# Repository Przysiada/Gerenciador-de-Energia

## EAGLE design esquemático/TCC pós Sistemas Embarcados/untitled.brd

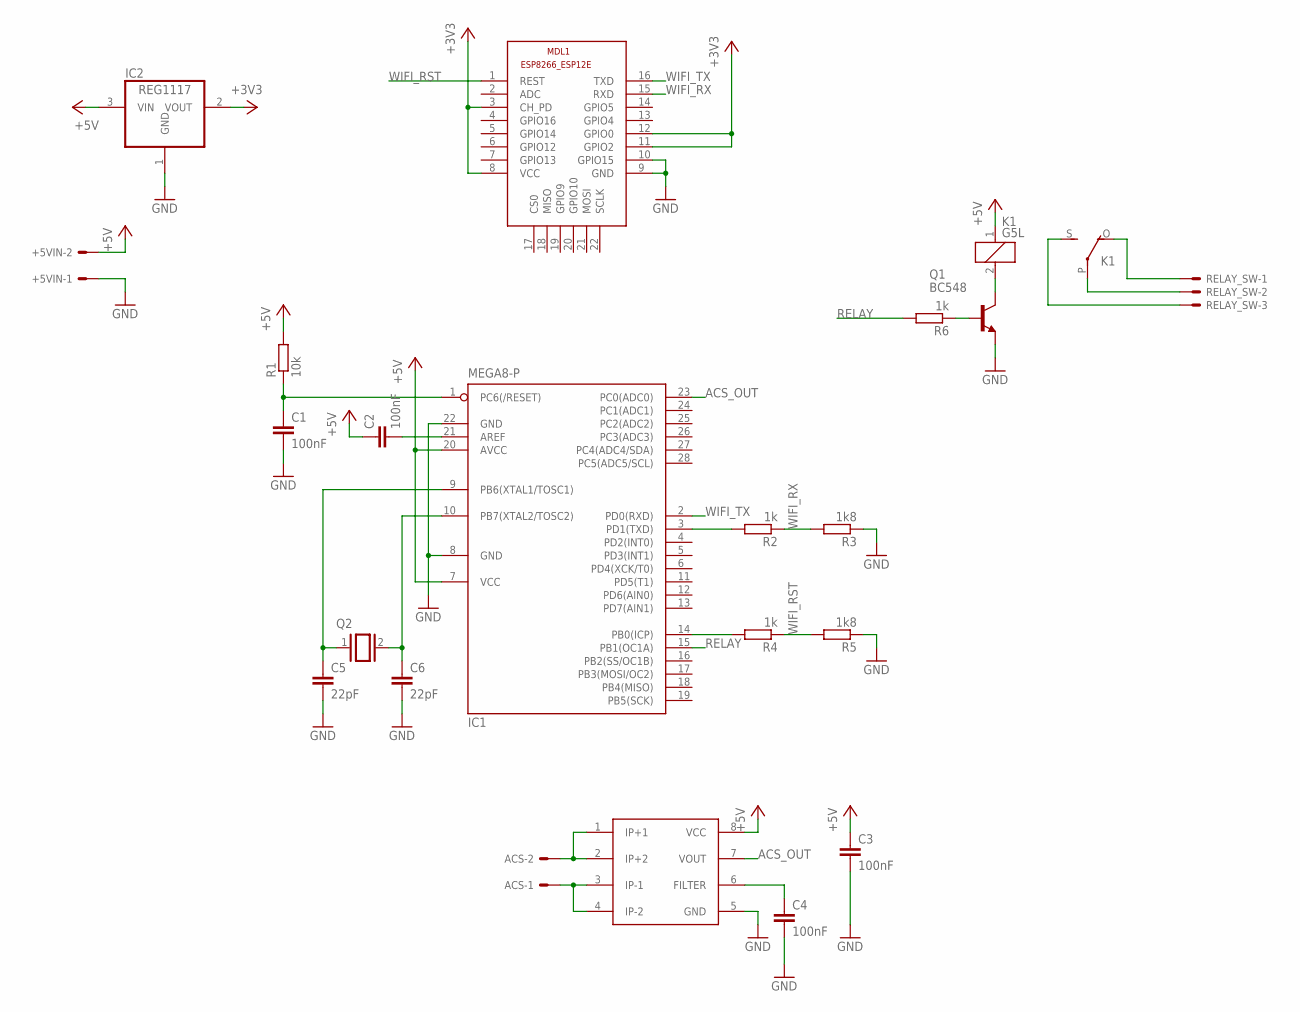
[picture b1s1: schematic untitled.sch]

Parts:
+5VIN: KK-156-2
ACS: KK-156-2
C1, C2, C3, C4: 100nF; C050-030X075
C5, C6: 22pF; C050-030X075
IC1: MEGA8-P; DIL28-3
IC2: REG1117; SOT223
K1: G5L; G5LE
MDL1: ESP8266-12EESP8266-ESP12E; ESP8266-ESP12E
Q1: BC548; TO92-EBC
Q2: XTAL/S; QS
R1: 10k; 0204/5
R2, R4, R6: 1k; 0204/5
R3, R5: 1k8; 0204/5
RELAY_SW: KK-156-3
U$1: ACS712; SO08

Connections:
+3V3: IC2.2 (VOUT), MDL1.3 (CH_PD), MDL1.8 (VCC), MDL1.11 (GPIO2), MDL1.12 (GPIO0)
+5V: +5VIN.2, C2.1, C3.1, IC1.7 (VCC), IC1.20 (AVCC), IC2.3 (VIN), K1.1, R1.2, U$1.8 (VCC)
ACS_OUT: IC1.23 (PC0(ADC0)), U$1.7 (VOUT)
GND: +5VIN.1, C1.2, C3.2, C4.2, C5.2, C6.2, IC1.8 (GND), IC1.22 (GND), IC2.1 (GND), MDL1.9 (GND), MDL1.10 (GPIO15), Q1.E, R3.1, R5.1, U$1.5 (GND)
unnamed: IC1.3 (PD1(TXD)), R2.2
unnamed: C2.2, IC1.21 (AREF)
unnamed: IC1.14 (PB0(ICP)), R4.2
unnamed: K1.2, Q1.C
unnamed: Q1.B, R6.1
unnamed: K1.P, RELAY_SW.2
unnamed: K1.O, RELAY_SW.1
unnamed: K1.S, RELAY_SW.3
unnamed: ACS.2, U$1.1 (IP+1), U$1.2 (IP+2)
unnamed: ACS.1, U$1.3 (IP-1), U$1.4 (IP-2)
unnamed: C5.1, IC1.9 (PB6(XTAL1/TOSC1)), Q2.1
unnamed: C6.1, IC1.10 (PB7(XTAL2/TOSC2)), Q2.2
unnamed: C1.1, IC1.1 (PC6(/RESET)), R1.1
unnamed: C4.1, U$1.6 (FILTER)
RELAY: IC1.15 (PB1(OC1A)), R6.2
WIFI_RST: MDL1.1 (REST), R4.1, R5.2
WIFI_RX: MDL1.15 (RXD), R2.1, R3.2
WIFI_TX: IC1.2 (PD0(RXD)), MDL1.16 (TXD)

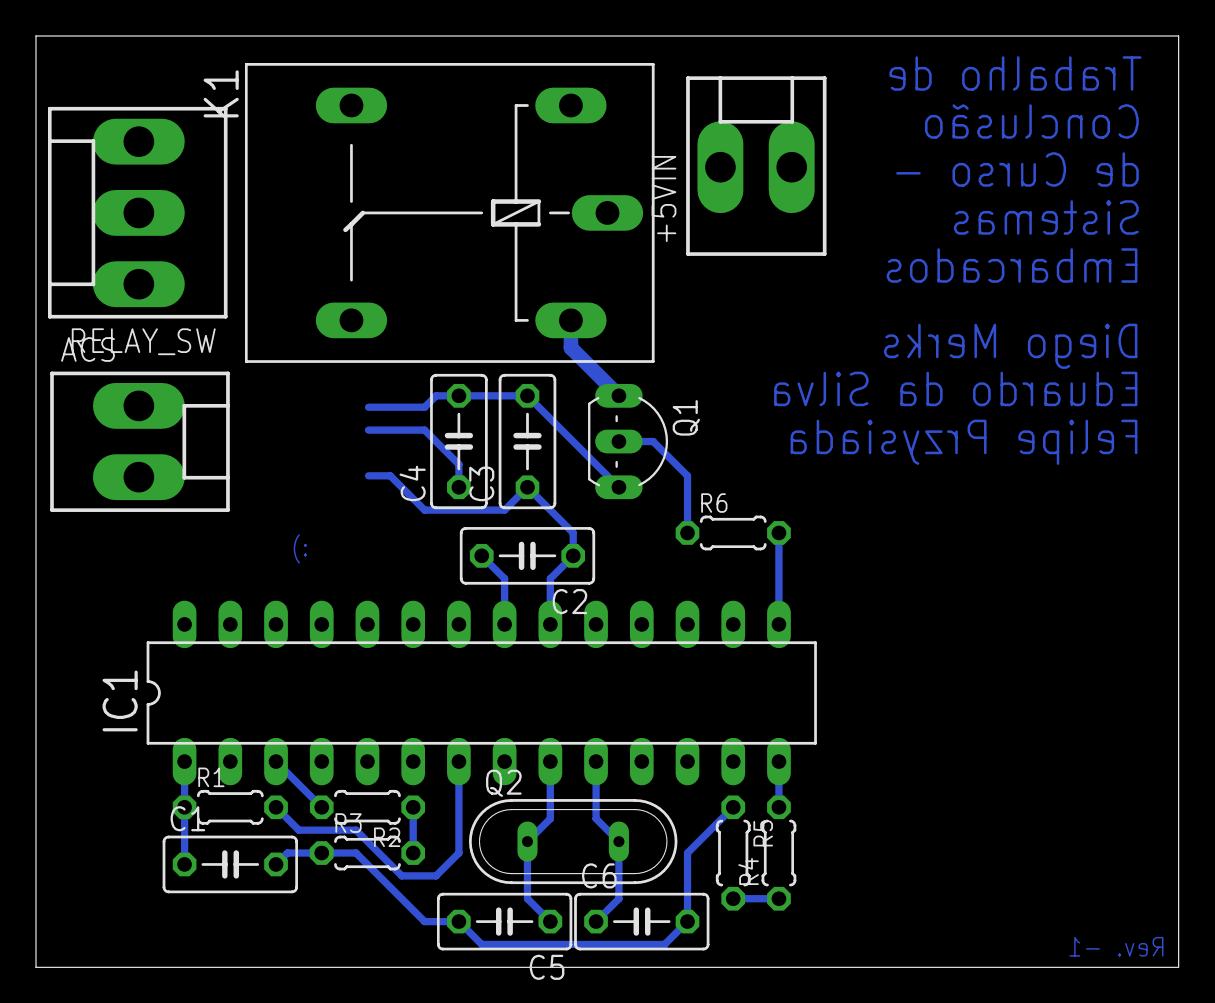
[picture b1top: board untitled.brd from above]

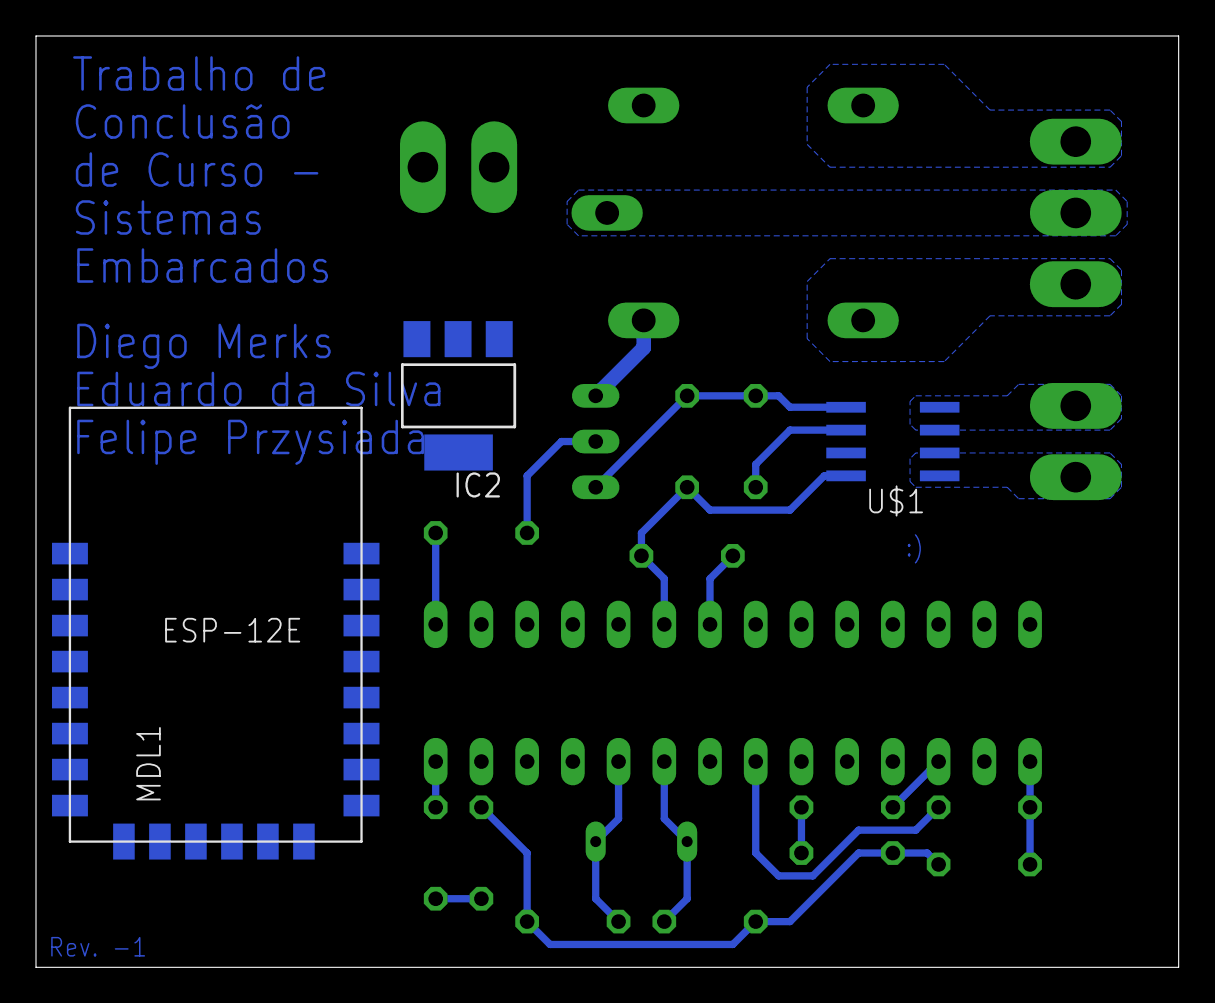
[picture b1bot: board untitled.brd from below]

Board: 2 copper layers, 63.5 x 51.7 mm, 22 parts (3 on the bottom side), 22 nets.

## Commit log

2019-10-15 Projeto Completo
